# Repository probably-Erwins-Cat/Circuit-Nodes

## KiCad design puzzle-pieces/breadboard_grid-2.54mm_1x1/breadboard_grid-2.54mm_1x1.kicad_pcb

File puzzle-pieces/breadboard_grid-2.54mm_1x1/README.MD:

# Breadboard grid (2.54 mm, 1×1)

This breadboard grid provides 2.54 mm spacing in a compact 1×1 layout for small prototypes and classroom exercises. It is useful when students need a small area to solder or test circuits while keeping components organised.

## Typical uses in circuits
- Small soldered circuits and stand-in for a full-size prototyping board.

## Practical and safety notes
- Use low voltages for classroom work and avoid mains-level experiments on these small boards.

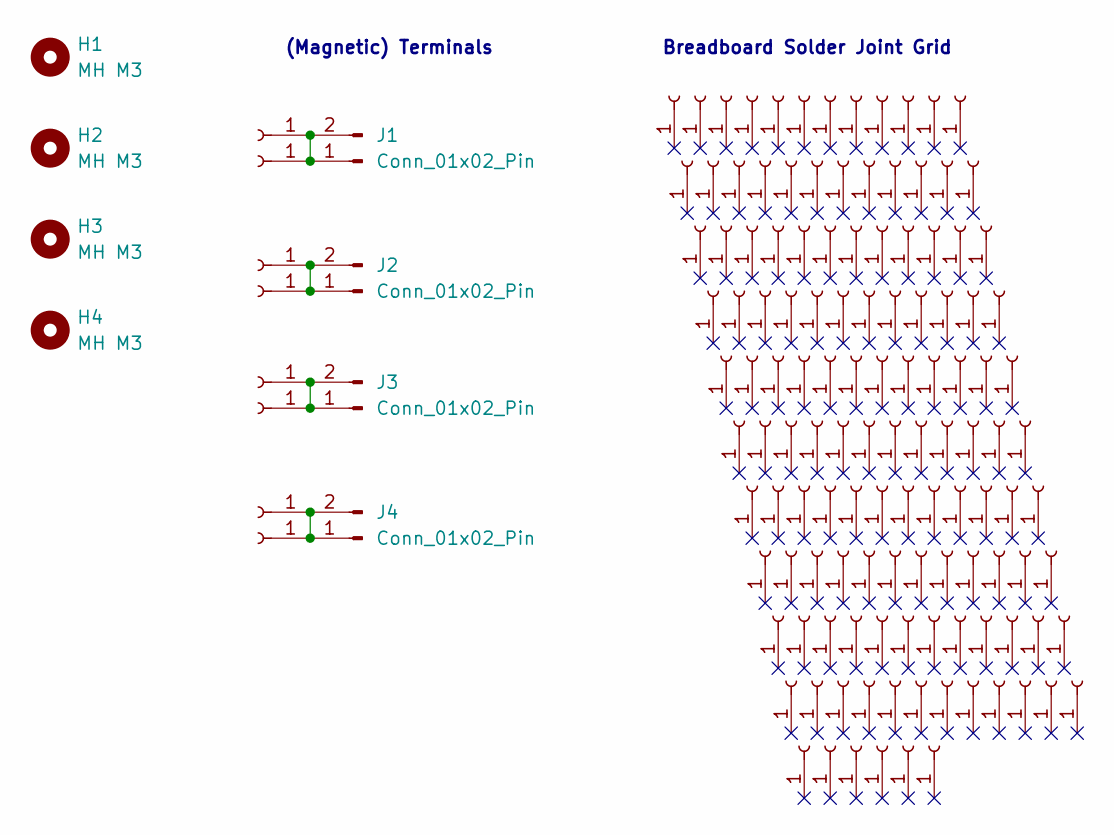
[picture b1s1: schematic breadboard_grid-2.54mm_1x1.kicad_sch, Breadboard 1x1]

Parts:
H1, H2, H3, H4: MH M3; MountingHole_3.0mm_M3_tight
J1, J2, J3, J4: Conn_01x02_Pin; Magnetic_Connector_1x02_P2.5mm_Horizontal_round-ears
J5, J6, J7, J10, J11, J12, J13, J14, J15, J16, J17, J18, J19, J20, J21, J22, J23, J24, J25, J26, J27, J28, J29, J30, J31, J32, J33, J34, J35, J36, J37, J38, J39, J40, J41, J42, J43, J44, J45, J46, J47, J48, J49, J50, J51, J52, J53, J54, J55, J56, J57, J58, J59, J60, J61, J62, J64, J65, J66, J67, J68, J69, J70, J71, J72, J73, J76, J77, J78, J79, J80, J81, J82, J83, J84, J85, J87, J88, J89, J90, J91, J92, J93, J94, J95, J96, J97, J98, J99, J100, J101, J102, J103, J104, J105, J106, J107, J108, J109, J110, J111, J112, J113, J114, J115, J116, J117, J118, J119, J120, J121, J122, J123, J124, J125, J126, J127, J128, J129, J130, J131, J132, J133, J134, J135, J136, J137, J138, J139, J142, J143, J144, J145, J146: Conn_01x01_Socket

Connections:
unnamed: J1.1, J1.2, J62.1, J98.1
unnamed: J4.1, J4.2, J51.1, J87.1
unnamed: J2.1, J2.2, J7.1, J10.1
unnamed: J3.1, J3.2, J139.1, J142.1

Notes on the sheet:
(Magnetic) Terminals
Breadboard Solder Joint Grid

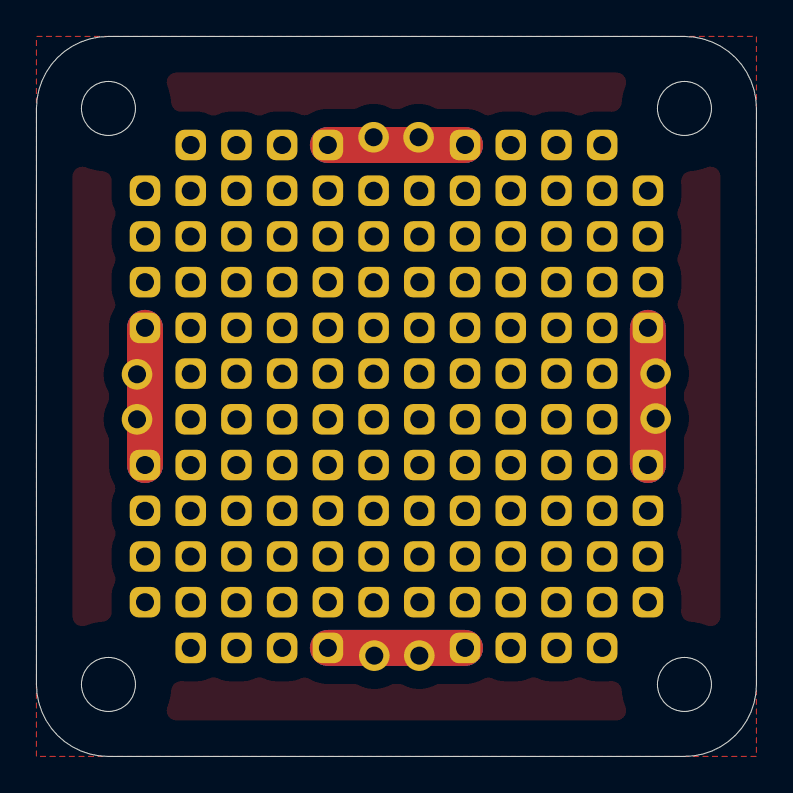
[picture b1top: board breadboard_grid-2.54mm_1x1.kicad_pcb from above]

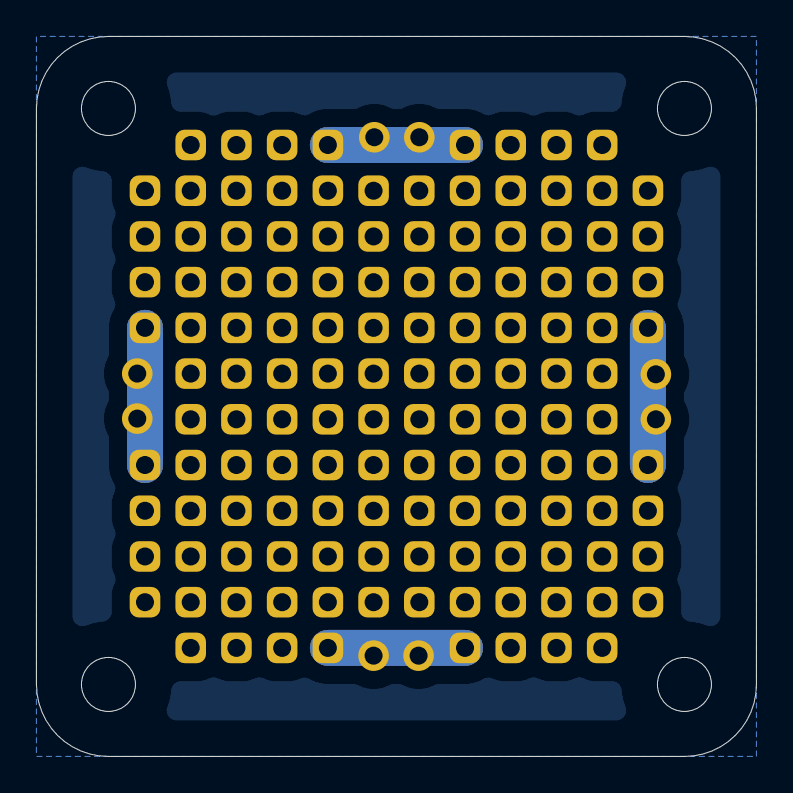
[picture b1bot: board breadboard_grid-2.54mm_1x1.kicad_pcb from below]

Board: 2 copper layers, 40.0 x 40.0 mm, 140 parts (132 on the bottom side), 4 nets.

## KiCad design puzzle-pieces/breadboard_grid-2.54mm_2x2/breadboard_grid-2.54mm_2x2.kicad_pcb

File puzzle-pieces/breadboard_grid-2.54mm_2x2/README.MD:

# Breadboard Grid 2×2 (2.54 mm Spacing)

This puzzle piece is a generic breadboard grid with 2.54 mm spacing—the standard spacing used in most hobbyist electronics. It serves as a placeholder for building more complex custom circuits that don't fit neatly into predefined puzzle pieces. You can solder your own components directly onto this breadboard area. It exists in various sizes (1×1, 1×2, 2×2, and larger).

The square holes have rounded corners, which accommodates not only traditional through-hole parts but also larger SMT (surface-mount technology) components, though the holes are optimized for through-hole use.

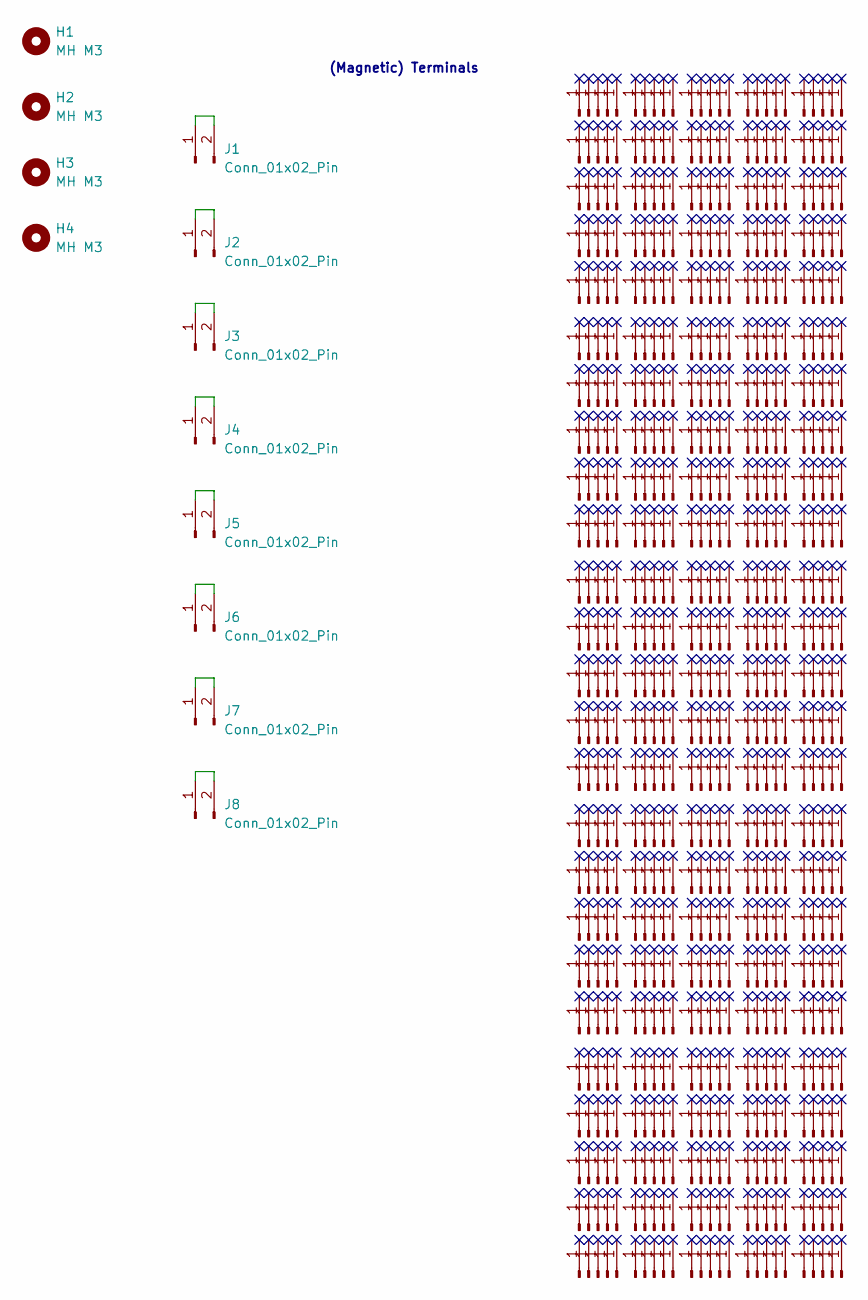
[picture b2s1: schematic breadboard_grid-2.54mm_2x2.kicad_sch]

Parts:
H1, H2, H3, H4: MH M3; MountingHole_3.0mm_M3_tight
J1, J2, J3, J4, J5, J6, J7, J8: Conn_01x02_Pin; Magnetic_Connector_1x02_P2.5mm_Horizontal_round-ears
SJ1, SJ2, SJ3, SJ4, SJ5, SJ6, SJ7, SJ8, SJ9, SJ10, SJ11, SJ12, SJ13, SJ14, SJ15, SJ16, SJ17, SJ18, SJ19, SJ20, SJ21, SJ22, SJ23, SJ24, SJ25, SJ26, SJ27, SJ28, SJ29, SJ30, SJ31, SJ32, SJ33, SJ34, SJ35, SJ36, SJ37, SJ38, SJ39, SJ40, SJ41, SJ42, SJ43, SJ44, SJ45, SJ46, SJ47, SJ48, SJ49, SJ50, SJ51, SJ52, SJ53, SJ54, SJ55, SJ56, SJ57, SJ58, SJ59, SJ60, SJ61, SJ62, SJ63, SJ64, SJ65, SJ66, SJ67, SJ68, SJ69, SJ70, SJ71, SJ72, SJ73, SJ74, SJ75, SJ76, SJ77, SJ78, SJ79, SJ80, SJ81, SJ82, SJ83, SJ84, SJ85, SJ86, SJ87, SJ88, SJ89, SJ90, SJ91, SJ92, SJ93, SJ94, SJ95, SJ96, SJ97, SJ98, SJ99, SJ100, SJ101, SJ102, SJ103, SJ104, SJ105, SJ106, SJ107, SJ108, SJ109, SJ110, SJ111, SJ112, SJ113, SJ114, SJ115, SJ116, SJ117, SJ118, SJ119, SJ120, SJ121, SJ122, SJ123, SJ124, SJ125, SJ126, SJ127, SJ128, SJ129, SJ130, SJ131, SJ132, SJ133, SJ134, SJ135, SJ136, SJ137, SJ138, SJ139, SJ140, SJ141, SJ142, SJ143, SJ144, SJ145, SJ146, SJ147, SJ148, SJ149, SJ150, SJ151, SJ152, SJ153, SJ154, SJ155, SJ156, SJ157, SJ158, SJ159, SJ160, SJ161, SJ162, SJ163, SJ164, SJ165, SJ166, SJ167, SJ168, SJ169, SJ170, SJ171, SJ172, SJ173, SJ174, SJ175, SJ176, SJ177, SJ178, SJ179, SJ180, SJ181, SJ182, SJ183, SJ184, SJ185, SJ186, SJ187, SJ188, SJ189, SJ190, SJ191, SJ192, SJ193, SJ194, SJ195, SJ196, SJ197, SJ198, SJ199, SJ200, SJ201, SJ202, SJ203, SJ204, SJ205, SJ206, SJ207, SJ208, SJ209, SJ210, SJ211, SJ212, SJ213, SJ214, SJ215, SJ216, SJ217, SJ218, SJ219, SJ220, SJ221, SJ222, SJ223, SJ224, SJ225, SJ226, SJ227, SJ228, SJ229, SJ230, SJ231, SJ232, SJ233, SJ234, SJ235, SJ236, SJ237, SJ238, SJ239, SJ240, SJ241, SJ242, SJ243, SJ244, SJ245, SJ246, SJ247, SJ248, SJ249, SJ250, SJ251, SJ252, SJ253, SJ254, SJ255, SJ256, SJ257, SJ258, SJ259, SJ260, SJ261, SJ262, SJ263, SJ264, SJ265, SJ266, SJ267, SJ268, SJ269, SJ270, SJ271, SJ272, SJ273, SJ274, SJ275, SJ276, SJ277, SJ278, SJ279, SJ280, SJ281, SJ282, SJ283, SJ284, SJ285, SJ286, SJ287, SJ288, SJ289, SJ290, SJ291, SJ292, SJ293, SJ294, SJ295, SJ296, SJ297, SJ298, SJ299, SJ300, SJ301, SJ302, SJ303, SJ304, SJ305, SJ306, SJ307, SJ308, SJ309, SJ310, SJ311, SJ312, SJ313, SJ314, SJ315, SJ316, SJ317, SJ318, SJ319, SJ320, SJ321, SJ322, SJ323, SJ324, SJ325, SJ326, SJ327, SJ328, SJ329, SJ330, SJ331, SJ332, SJ333, SJ334, SJ335, SJ336, SJ337, SJ338, SJ339, SJ340, SJ341, SJ342, SJ343, SJ344, SJ345, SJ346, SJ347, SJ348, SJ349, SJ350, SJ351, SJ352, SJ353, SJ354, SJ355, SJ356, SJ357, SJ358, SJ359, SJ360, SJ361, SJ362, SJ363, SJ364, SJ365, SJ366, SJ367, SJ368, SJ369, SJ370, SJ371, SJ372, SJ373, SJ374, SJ375, SJ376, SJ377, SJ378, SJ379, SJ380, SJ381, SJ382, SJ383, SJ384, SJ385, SJ386, SJ387, SJ388, SJ389, SJ390, SJ391, SJ392, SJ393, SJ394, SJ395, SJ396, SJ397, SJ398, SJ399, SJ400, SJ401, SJ402, SJ403, SJ404, SJ405, SJ406, SJ407, SJ408, SJ409, SJ410, SJ411, SJ412, SJ413, SJ414, SJ415, SJ416, SJ417, SJ418, SJ419, SJ420, SJ421, SJ422, SJ423, SJ424, SJ425, SJ426, SJ427, SJ428, SJ429, SJ430, SJ431, SJ432, SJ433, SJ434, SJ435, SJ436, SJ437, SJ438, SJ439, SJ440, SJ441, SJ442, SJ443, SJ444, SJ445, SJ446, SJ447, SJ448, SJ449, SJ450, SJ451, SJ452, SJ453, SJ454, SJ455, SJ456, SJ457, SJ458, SJ459, SJ460, SJ461, SJ462, SJ463, SJ464, SJ465, SJ466, SJ467, SJ468, SJ469, SJ470, SJ471, SJ472, SJ473, SJ474, SJ475, SJ476, SJ477, SJ478, SJ479, SJ480, SJ481, SJ482, SJ483, SJ484, SJ485, SJ486, SJ487, SJ488, SJ489, SJ490, SJ491, SJ492, SJ493, SJ494, SJ495, SJ496, SJ497, SJ498, SJ499, SJ500, SJ501, SJ502, SJ503, SJ504, SJ505, SJ506, SJ507, SJ508, SJ509, SJ510, SJ511, SJ512, SJ513, SJ514, SJ515, SJ516, SJ517, SJ518, SJ519, SJ520, SJ521, SJ522, SJ523, SJ524, SJ525, SJ526, SJ527, SJ528, SJ529, SJ530, SJ531, SJ532, SJ533, SJ534, SJ535, SJ536, SJ537, SJ538, SJ539, SJ540, SJ541, SJ542, SJ543, SJ544, SJ545, SJ546, SJ547, SJ548, SJ549, SJ550, SJ551, SJ552, SJ553, SJ554, SJ555, SJ556, SJ557, SJ558, SJ559, SJ560, SJ561, SJ562, SJ563, SJ564, SJ565, SJ566, SJ567, SJ568, SJ569, SJ570, SJ571, SJ572, SJ573, SJ574, SJ575, SJ576, SJ577, SJ578, SJ579, SJ580, SJ581, SJ582, SJ583, SJ584, SJ585, SJ586, SJ587, SJ588, SJ589, SJ590, SJ591, SJ592, SJ593, SJ594, SJ595, SJ596, SJ597, SJ598, SJ599, SJ600, SJ601, SJ602, SJ603, SJ604, SJ605, SJ606, SJ607, SJ608, SJ609, SJ610, SJ611, SJ612, SJ613, SJ614, SJ615, SJ616, SJ617, SJ618, SJ619, SJ620, SJ621, SJ622, SJ623, SJ624, SJ625: Pin; THTPad_for-2.54mm-breadboard

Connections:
unnamed: J1.1, J1.2
unnamed: J2.1, J2.2
unnamed: J3.1, J3.2
unnamed: J4.1, J4.2
unnamed: J5.1, J5.2
unnamed: J6.1, J6.2
unnamed: J7.1, J7.2
unnamed: J8.1, J8.2

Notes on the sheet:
(Magnetic) Terminals

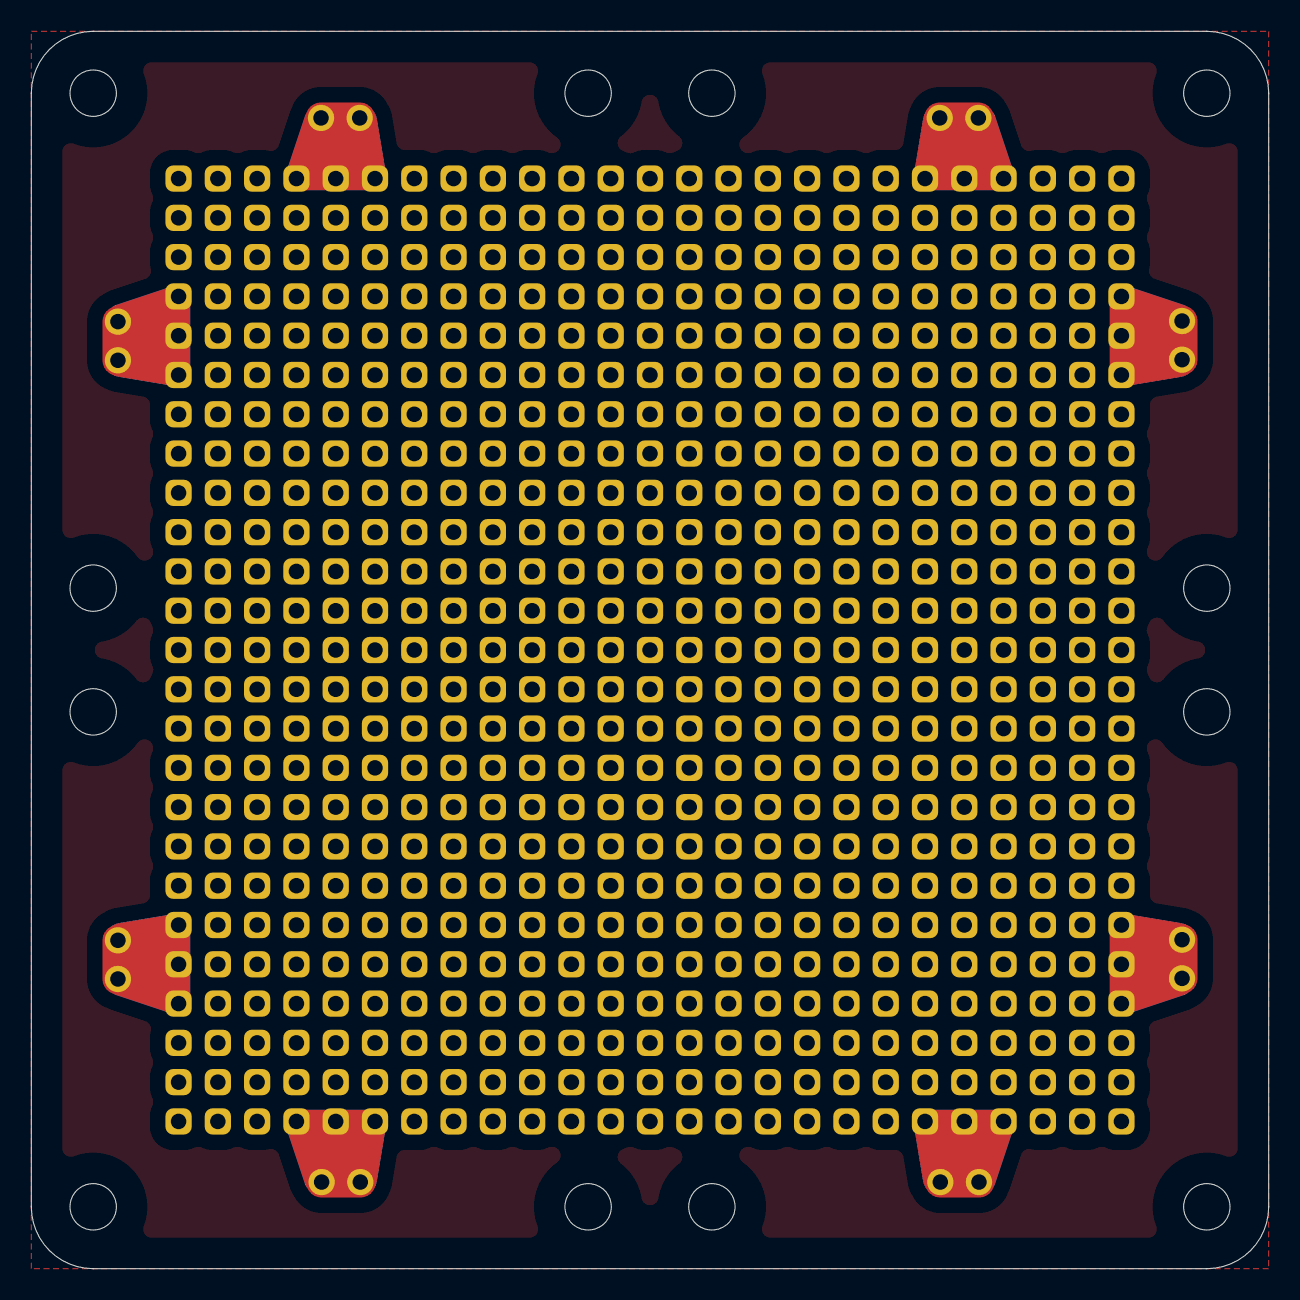
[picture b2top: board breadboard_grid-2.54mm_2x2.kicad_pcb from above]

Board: 2 copper layers, 80.0 x 80.0 mm, 645 parts (0 on the bottom side), 8 nets.

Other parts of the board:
H2#2, H2#3, H2#4, H2#5, H4#2, H4#3, H4#4, H4#5: MH M3; MountingHole_3.0mm_M3_tight

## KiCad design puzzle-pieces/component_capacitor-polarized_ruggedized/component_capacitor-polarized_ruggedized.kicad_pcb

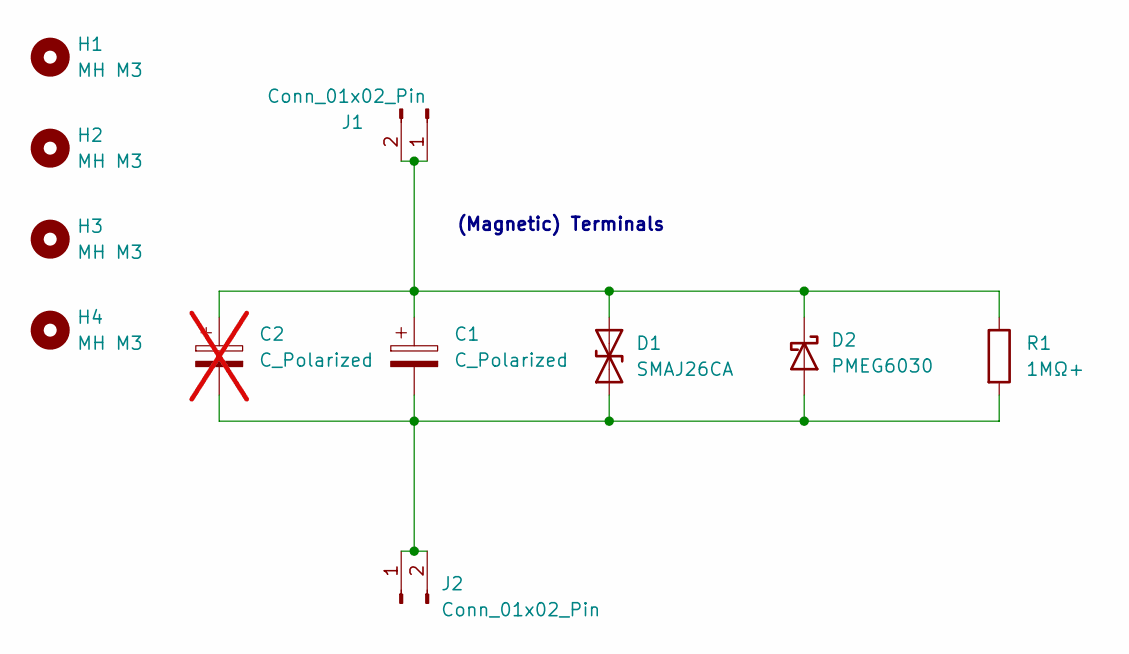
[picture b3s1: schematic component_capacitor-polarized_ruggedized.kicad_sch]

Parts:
C1: C_Polarized; CP_Radial_D8.0mm_P5.00mm
C2: C_Polarized; CP_Elec_10x12.5; not fitted
D1: SMAJ26CA; D_SMA_Handsoldering; LCSC C908826
D2: PMEG6030; D_SOD-128; LCSC C53114036
H1, H2, H3, H4: MH M3; MountingHole_3.0mm_M3_tight
J1, J2: Conn_01x02_Pin; Magnetic_Connector_1x02_P2.5mm_Horizontal_round-ears
R1: 1MΩ+; R_1206_3216Metric_Pad1.30x1.75mm_HandSolder; LCSC C7250

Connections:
unnamed: C1.2, C2.2, D1.1 (A1), D2.2 (A), J2.1, J2.2, R1.2
unnamed: C1.1, C2.1, D1.2 (A2), D2.1 (K), J1.1, J1.2, R1.1

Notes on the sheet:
(Magnetic) Terminals

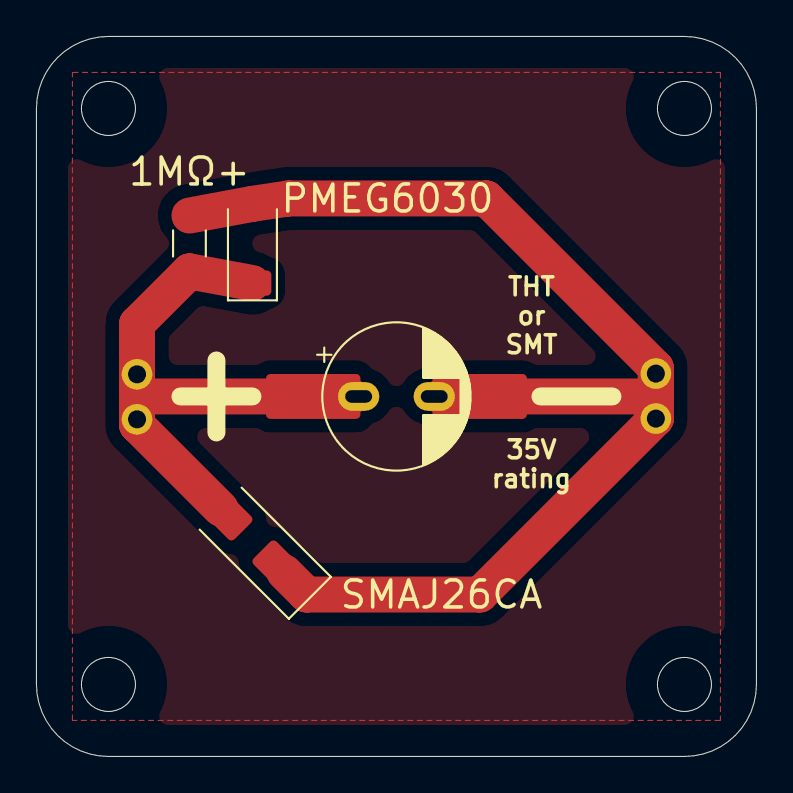
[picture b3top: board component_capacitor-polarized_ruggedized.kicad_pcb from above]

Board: 2 copper layers, 40.0 x 40.0 mm, 10 parts (0 on the bottom side), 2 nets.

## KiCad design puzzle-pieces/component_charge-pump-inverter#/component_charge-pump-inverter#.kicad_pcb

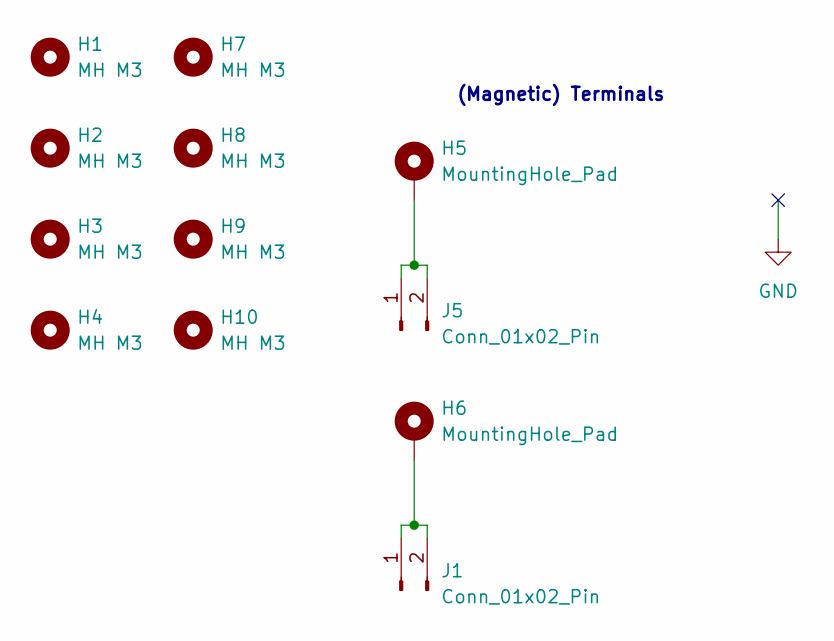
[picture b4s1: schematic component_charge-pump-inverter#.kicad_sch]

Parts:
H1, H2, H3, H4, H7, H8, H9, H10: MH M3; MountingHole_3.0mm_M3_tight
H5, H6: MountingHole_Pad; MountingHole_6mm_Node
J1, J5: Conn_01x02_Pin; Magnetic_Connector_1x02_P2.5mm_Horizontal_round-ears

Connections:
unnamed: H6.1, J1.1, J1.2
unnamed: H5.1, J5.1, J5.2

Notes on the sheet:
(Magnetic) Terminals

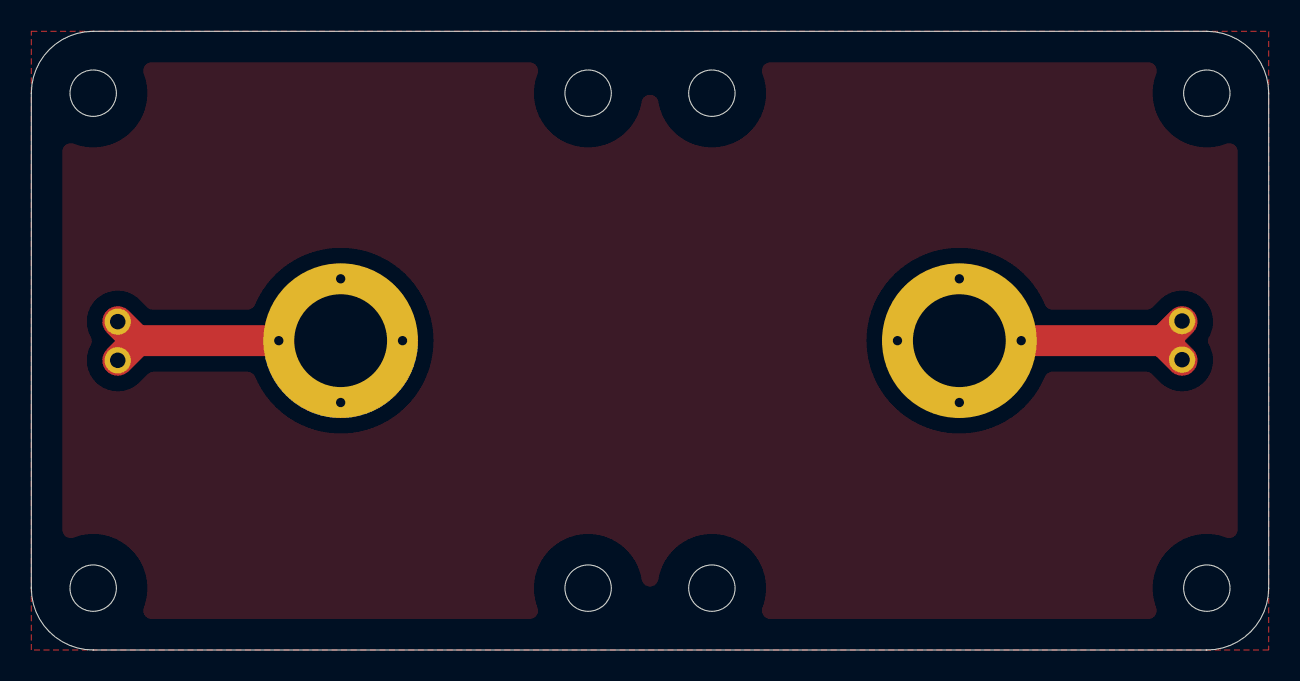
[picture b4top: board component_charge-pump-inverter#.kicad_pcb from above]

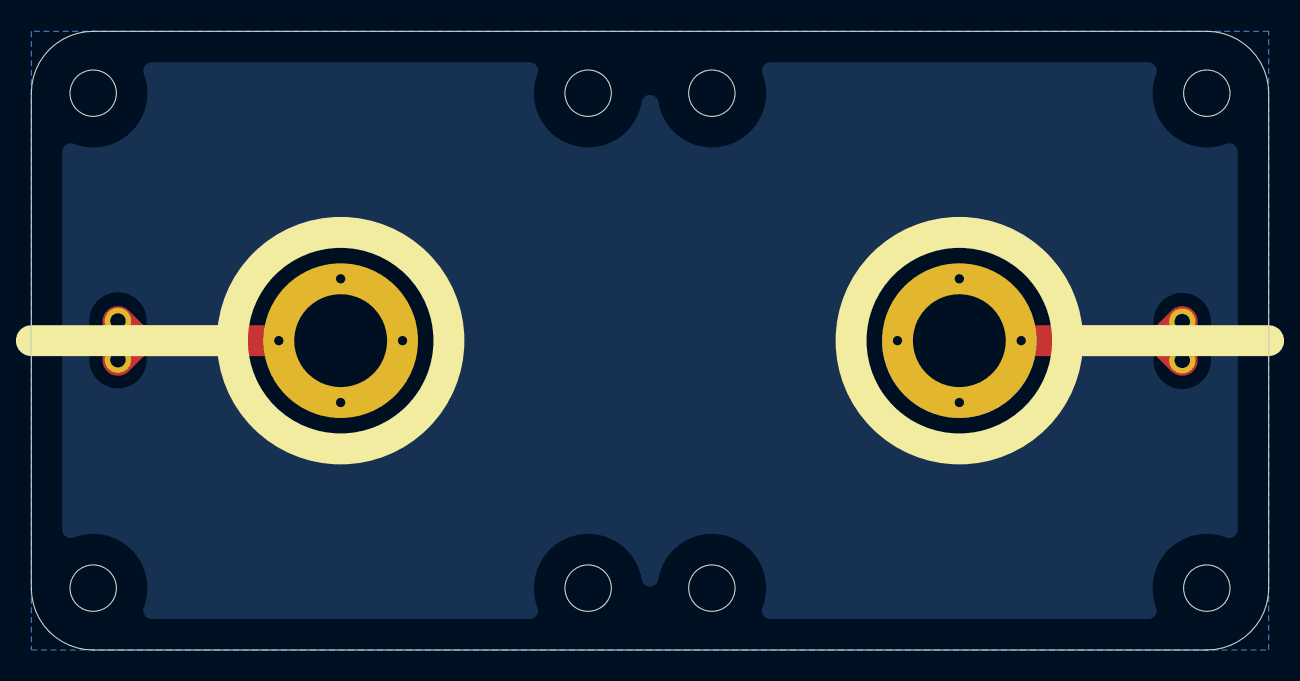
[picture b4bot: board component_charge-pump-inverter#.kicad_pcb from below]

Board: 2 copper layers, 80.0 x 40.0 mm, 12 parts (5 on the bottom side), 2 nets.

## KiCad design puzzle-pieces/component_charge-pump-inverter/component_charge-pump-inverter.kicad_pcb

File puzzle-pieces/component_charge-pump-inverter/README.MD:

# Charge Pump Inverter (THT)

A charge-pump inverter converts a positive supply voltage into a corresponding negative voltage using capacitors and a high-frequency switching network. It is useful in classrooms for demonstrating how DC voltages can be level-shifted or inverted **without** inductors, making the underlying principle easy to observe and explain.

Charge Pumps do not have a dedicated symbol and are typically displayed with the bare components and IC. Since this is didactically not feasible herein, I invented a schematic symbol based on the schematic symbol of a (hydraulic) pump -- circle and large wedge -- and added a capacitor to it as well as indicated the flow directions, highlighting the input voltage levels and output voltage levels.

## Typical uses in circuits
- Generating a **–5 V** supply from a standard +5 V rail for experiments with operational amplifiers.
- Demonstrating **negative voltage generation** without inductors.
- Supplying simple analog circuits in “dual-supply” configurations (+5 V / GND / –5 V).
- Teaching switched-capacitor concepts and basic DC-DC conversion.

## Practical and safety notes
- The inverter can supply only **limited current**; loads below ~150 mA are recommended.  
- Larger output capacitors improve stability but increase inrush current at startup.
- Expect small amounts of ripple on the negative output due to the switching mechanism.
- Even though the board includes input protection, students should still adjust power supplies carefully.

# Essential parts (core charge pump)

These components form the functional DC-to-negative-DC converter:

- **Core IC:** LM2776 or compatible 2 MHz charge-pump inverter  
- **Input capacitor:** 10 µF X7R, 10–16 V 0805 or 1206
- **Flying capacitor:** 2.2–4.7 µF X7R 0805 or 1206
- **Output capacitor:** 4.7–10 µF X7R 0805 or 1206

These values improve stability and load behaviour while remaining fully within the LM2776 specifications.

# Recommended safety & protection parts

These components harden the module against common student errors (reverse polarity, overvoltage, accidental misconfiguration) without interfering with the functionality:

- **Reverse-polarity protection:** P-channel MOSFET (e.g., AO3401A)  
- **Over-voltage protection:** Bidirectional TVS diode, ~6 V standoff (e.g., SMF6.0CA)  
- **Short-circuit protection:** Polyfuse (PTC) on the input for additional abuse resistance, see dedicated polyfuse Circuit Node

These parts are not strictly required for operation but significantly increase longevity and safety in classroom environments. If you do **not** require internal safety (because you have other external safety), you can bridge the solder jumper and leave the safety parts unpopulated.

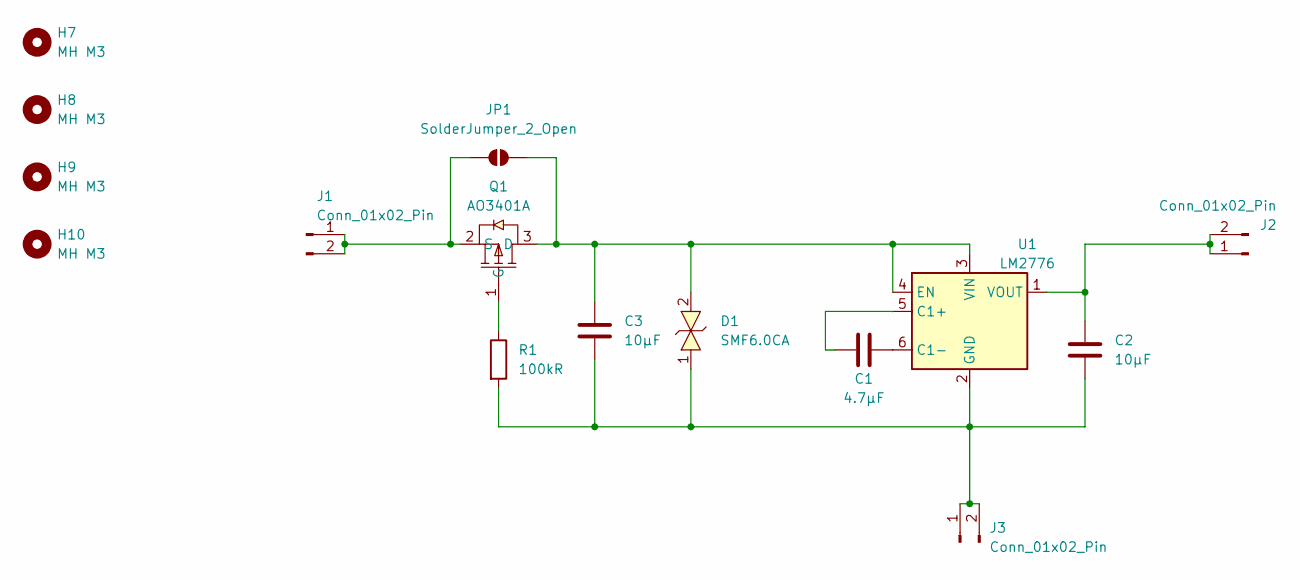
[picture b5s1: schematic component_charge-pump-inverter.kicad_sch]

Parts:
C1: 4.7µF; C_0805_2012Metric_Pad1.18x1.45mm_HandSolder
C2, C3: 10µF; C_0805_2012Metric_Pad1.18x1.45mm_HandSolder; LCSC C15850
D1: SMF6.0CA; SOD-123FL_L2.8-W1.8-LS3.7-BI; LCSC Part C2836402
H7, H8, H9, H10: MH M3; MountingHole_3.0mm_M3_tight
J1, J2, J3: Conn_01x02_Pin; Magnetic_Connector_1x02_P2.5mm_Horizontal_round-ears
JP1: SolderJumper_2_Open; SolderJumper-2_P1.3mm_Open_RoundedPad1.0x1.5mm
Q1: AO3401A; SOT-23-3_L2.9-W1.6-P1.90-LS2.8-BR; LCSC Part C5224202
R1: 100kR; R_0805_2012Metric_Pad1.20x1.40mm_HandSolder; LCSC C149504
U1: LM2776; SOT-23-6; LCSC C69527

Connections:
unnamed: J1.1, J1.2, JP1.1 (A), Q1.2 (S)
unnamed: C2.1, J2.1, J2.2, U1.1 (VOUT)
unnamed: C2.2, C3.2, D1.1, J3.1, J3.2, R1.2, U1.2 (GND)
unnamed: C3.1, D1.2, JP1.2 (B), Q1.3 (D), U1.3 (VIN), U1.4 (EN)
unnamed: Q1.1 (G), R1.1
unnamed: C1.1, U1.5 (C1+)
unnamed: C1.2, U1.6 (C1-)

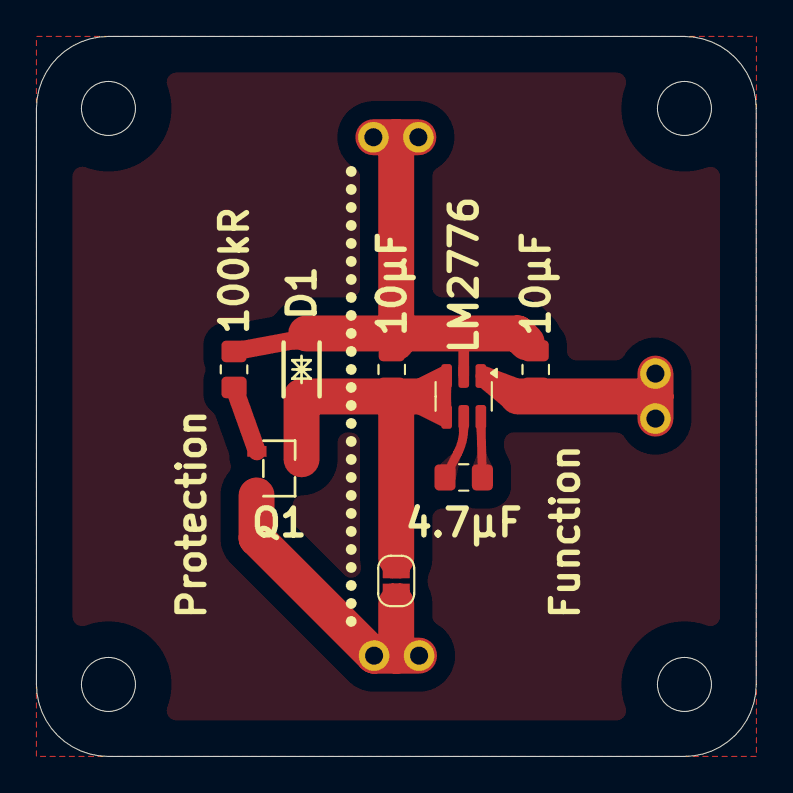
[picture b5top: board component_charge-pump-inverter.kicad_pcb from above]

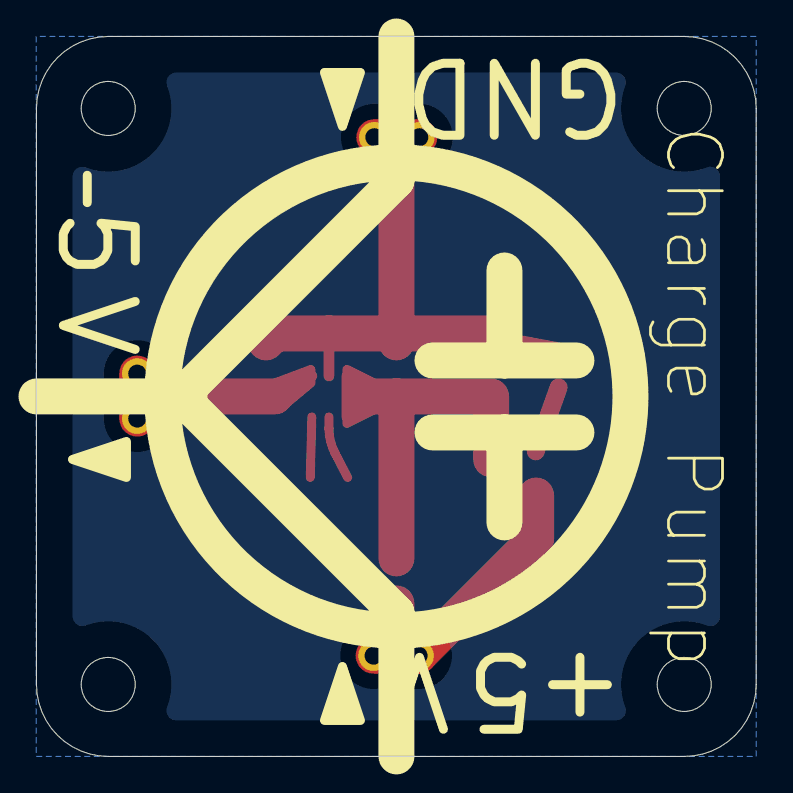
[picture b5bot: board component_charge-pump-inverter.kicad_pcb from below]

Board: 2 copper layers, 40.0 x 40.0 mm, 15 parts (4 on the bottom side), 7 nets.

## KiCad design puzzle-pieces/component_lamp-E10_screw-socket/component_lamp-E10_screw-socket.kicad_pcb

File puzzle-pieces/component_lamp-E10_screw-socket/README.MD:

# Lamp (E10, Screw Socket)

A small E10 lamp makes electrical effects visible through light and heat, and is a useful demonstration component in early lessons. Unlike a simple resistor, the filament’s resistance typically increases with temperature, so lamp behaviour is nonlinear.

# Typical uses in circuits
- Visual indicator for current flow in simple series circuits and for illustrating thermal effects in resistive elements.

# Practical and safety notes
- Select lamp voltage to match your supply to avoid excessive current or rapid burnout.
- Some LED-based E10 bulbs are polar and behave differently from incandescent lamps; treat them as diodes and use a series resistor when appropriate.

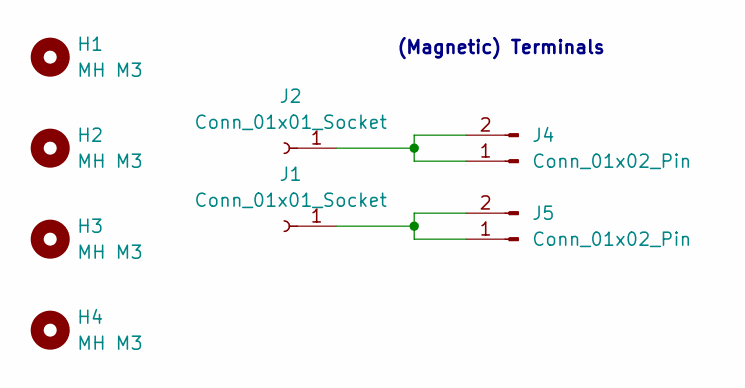
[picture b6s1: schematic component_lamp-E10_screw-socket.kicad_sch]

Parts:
H1, H2, H3, H4: MH M3; MountingHole_3.0mm_M3_tight
J1, J2: Conn_01x01_Socket; SolderWire-4sqmm_1x01_D3mm_OD6mm
J4, J5: Conn_01x02_Pin; Magnetic_Connector_1x02_P2.5mm_Horizontal_round-ears

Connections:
unnamed: J1.1 (Pin_1_1), J5.1, J5.2
unnamed: J2.1 (Pin_1_1), J4.1, J4.2

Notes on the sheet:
(Magnetic) Terminals

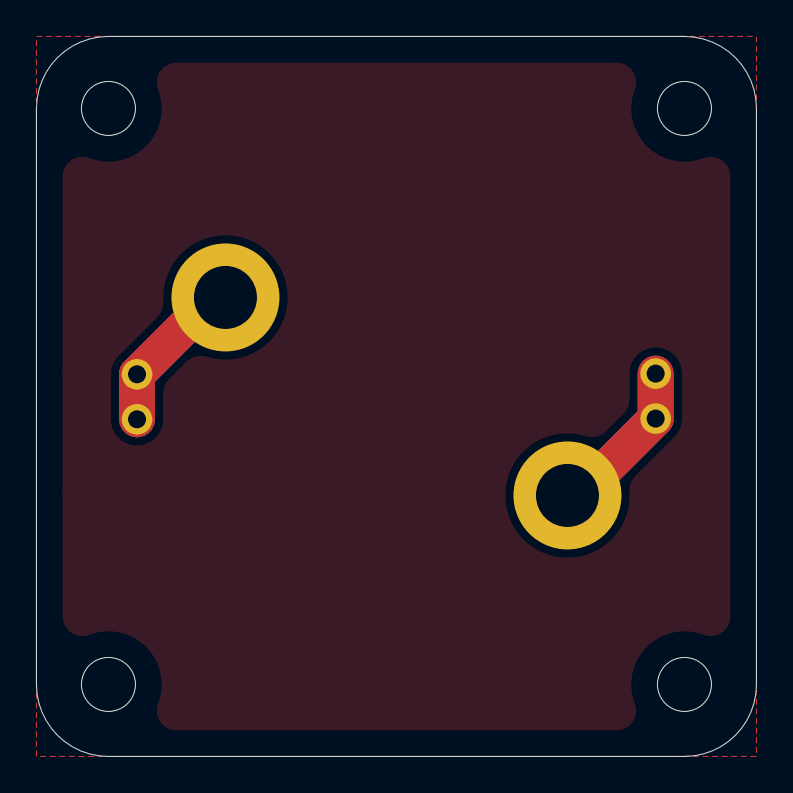
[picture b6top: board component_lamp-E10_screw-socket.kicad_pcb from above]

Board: 2 copper layers, 40.0 x 40.0 mm, 8 parts (0 on the bottom side), 2 nets.
